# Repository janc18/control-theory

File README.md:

# Features
- Isolated plant
- Plant-ID, Plant cal-data (eeprom)
- USB-PD powered

# Design

# BOM
## Main Board

|Component|Price|Characteristics|
|--|--|--|
|[ST STM32H7R3V8T6](https://www.st.com/resource/en/datasheet/stm32h7r3a8.pdf)| 7.89 USD| 600 Mhz, 67 GPIO|
|[FTDI FT232HL](https://ftdichip.com/products/ft232hl/)|4.09 USD| USB Hi-Speed to Single Channel Serial UART/FIFO/JTAG/SPI/I2C IC, LQFP-48|
|[TX24-30R-6ST-H1E](https://www.jae.com/direct/topics/topics_file_download/?topics_id=66728&ext_no=06)|1.36 USD|Board-to-Board Connector, parallel/ vertical, 30 pos., 1.27mm pitch, Receptacle|
|[TX25-30P-6ST-H1E](https://www.jae.com/direct/topics/topics_file_download/?topics_id=66780&ext_no=06)|0.98 USD|Board-to-Board Connector, parallel/ vertical, 30 pos., 1.27mm pitch, Plug|
|USB type C Connector|||
|DC DC Converter|||
|Mix Components(Leds)|||
|[ST STUSB4500](https://www.st.com/resource/en/datasheet/stusb4500.pdf)|1.91 USD|Standalone USB PD sink controller with short-to-VBUS protections|
|[TI ISO7760](https://www.ti.com/lit/gpn/iso7760)|2.59 USD| Robust EMC, six-channel, 6/0, reinforced digital isolator|

## Connector power rails:
- 3.3 V: LDO generated
- 5 V: USB or Buck converter
- 12 V: PD (optional)
- 20 V: PD (optional)

## FT232HL
### Requirements
To use any kind of interface (SPI, I2c, JTAG, or a proprietary protocol) it's require to send commands down the data stream
- 12Mhz oscillator
- [External EEPROM - 93LC56BT-I/OT](https://ww1.microchip.com/downloads/en/DeviceDoc/21794G.pdf) 
- LC Filter

# INFO
[A Primer on USB Type-C® and USB Power Delivery Applications and Requirements](https://www.ti.com/lit/SLYY109B) \
[USB PD: Power Delivery for Your Next Project](https://resources.altium.com/p/usb-power-delivery-your-next-project) \
[AN232B-04 Data Throughput, Latency and Handshaking](https://ftdichip.com/wp-content/uploads/2020/08/AN232B-04_DataLatencyFlow.pdf)\
[FT2232D/H Fast Opto-Isolated Serial Interface Mode](https://www.ftdichip.com/Support/Documents/AppNotes/AN_131_FT2232D_H_Fast%20Opto-Isolated%20Serial%20Interface%20mode.pdf)\
[N2232-02 Bit Mode Functions for the FT223](https://www.ftdichip.com/Documents/AppNotes/AN2232C-02_FT2232CBitMode.pdf)\
[Examples  for the JTAG interface with Labview](https://ftdichip.com/software-examples/mpsse-projects/ftcjtag-examples/)

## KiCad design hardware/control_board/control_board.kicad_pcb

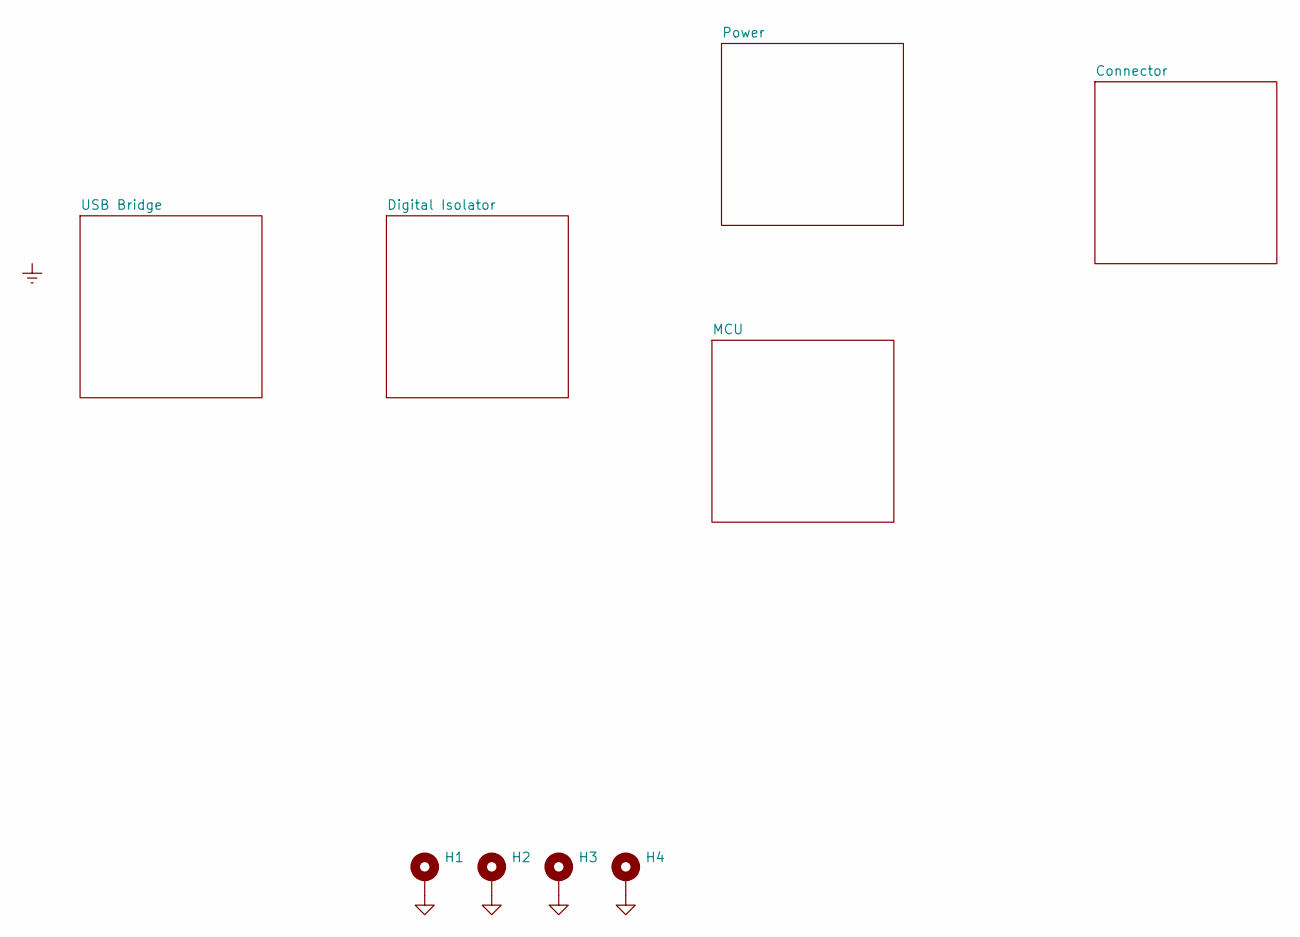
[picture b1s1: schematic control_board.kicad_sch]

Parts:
H1, H2, H3, H4: MountingHole_Pad; MountingHole_3.2mm_M3_Pad_Via

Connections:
GND: H1.1, H2.1, H3.1, H4.1

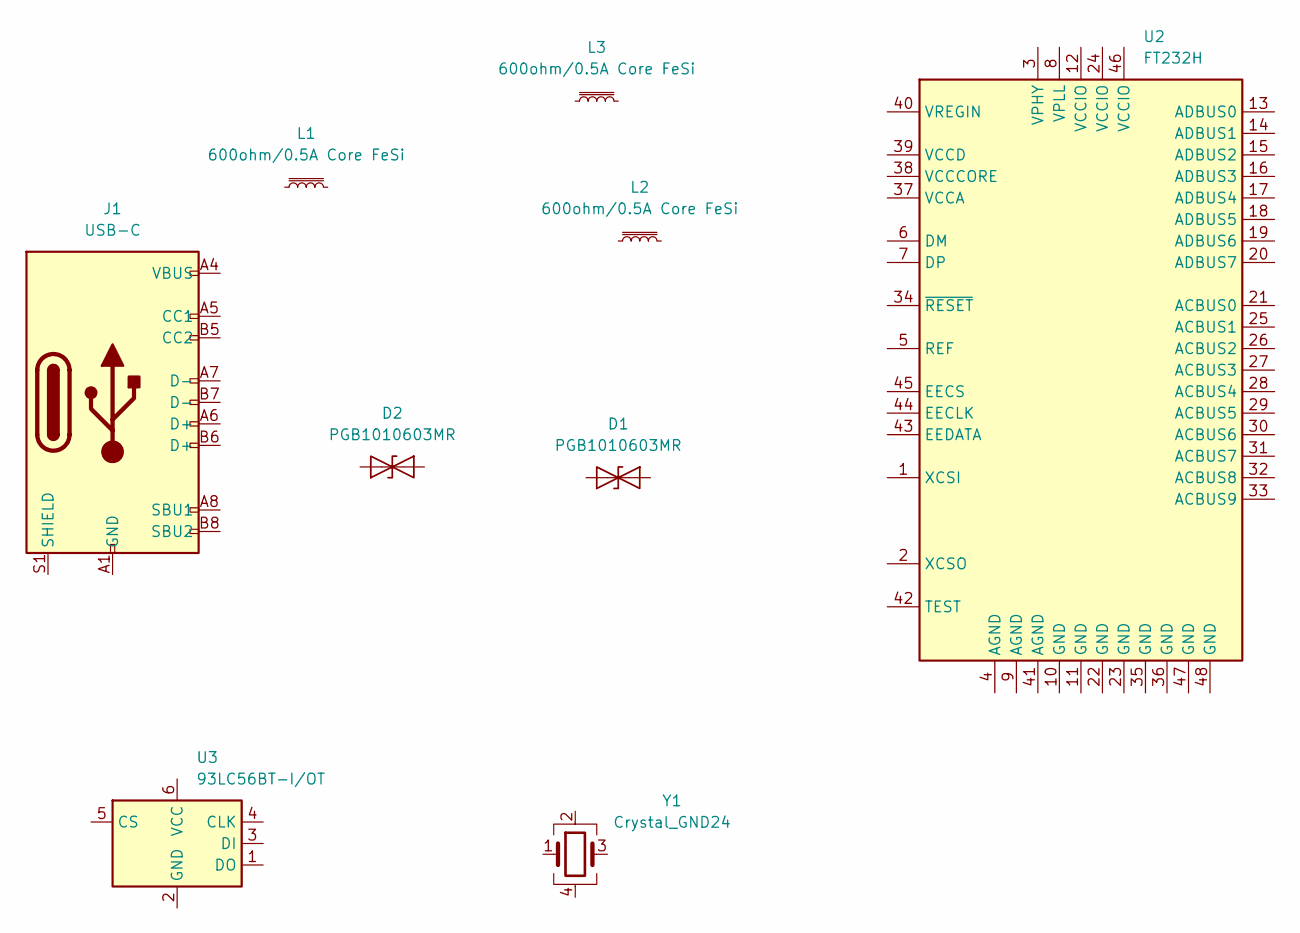
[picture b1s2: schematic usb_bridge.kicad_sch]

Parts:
D1, D2: PGB1010603MR; D_0603_1608Metric
J1: USB-C
L1, L2, L3: 600ohm/0.5A Core FeSi; L_0603_1608Metric
U2: FT232H; NXP_LQFN-48-1EP_7x7mm_P0.5mm_EP3.5x3.5mm_16xMask0.45x0.45
U3: 93LC56BT-I/OT; SOT-23-6
Y1: Crystal_GND24; Crystal_SMD_SeikoEpson_FA238V-4Pin_3.2x2.5mm

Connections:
unnamed: J1.A1 (GND), J1.A12 (GND), J1.B1 (GND), J1.B12 (GND)
unnamed: J1.A4 (VBUS), J1.A9 (VBUS), J1.B4 (VBUS), J1.B9 (VBUS)

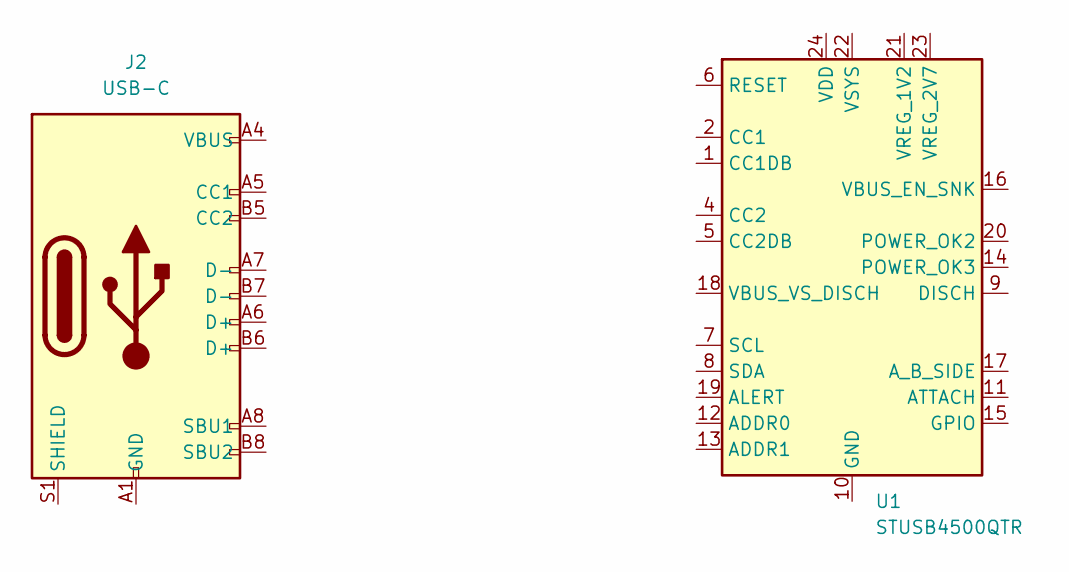
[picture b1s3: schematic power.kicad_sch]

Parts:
J2: USB-C
U1: STUSB4500QTR; QFN-24-1EP_4x4mm_P0.5mm_EP2.7x2.7mm

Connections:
unnamed: J2.A1 (GND), J2.A12 (GND), J2.B1 (GND), J2.B12 (GND)
unnamed: J2.A4 (VBUS), J2.A9 (VBUS), J2.B4 (VBUS), J2.B9 (VBUS)
unnamed: U1.10 (GND), U1.25 (GND)

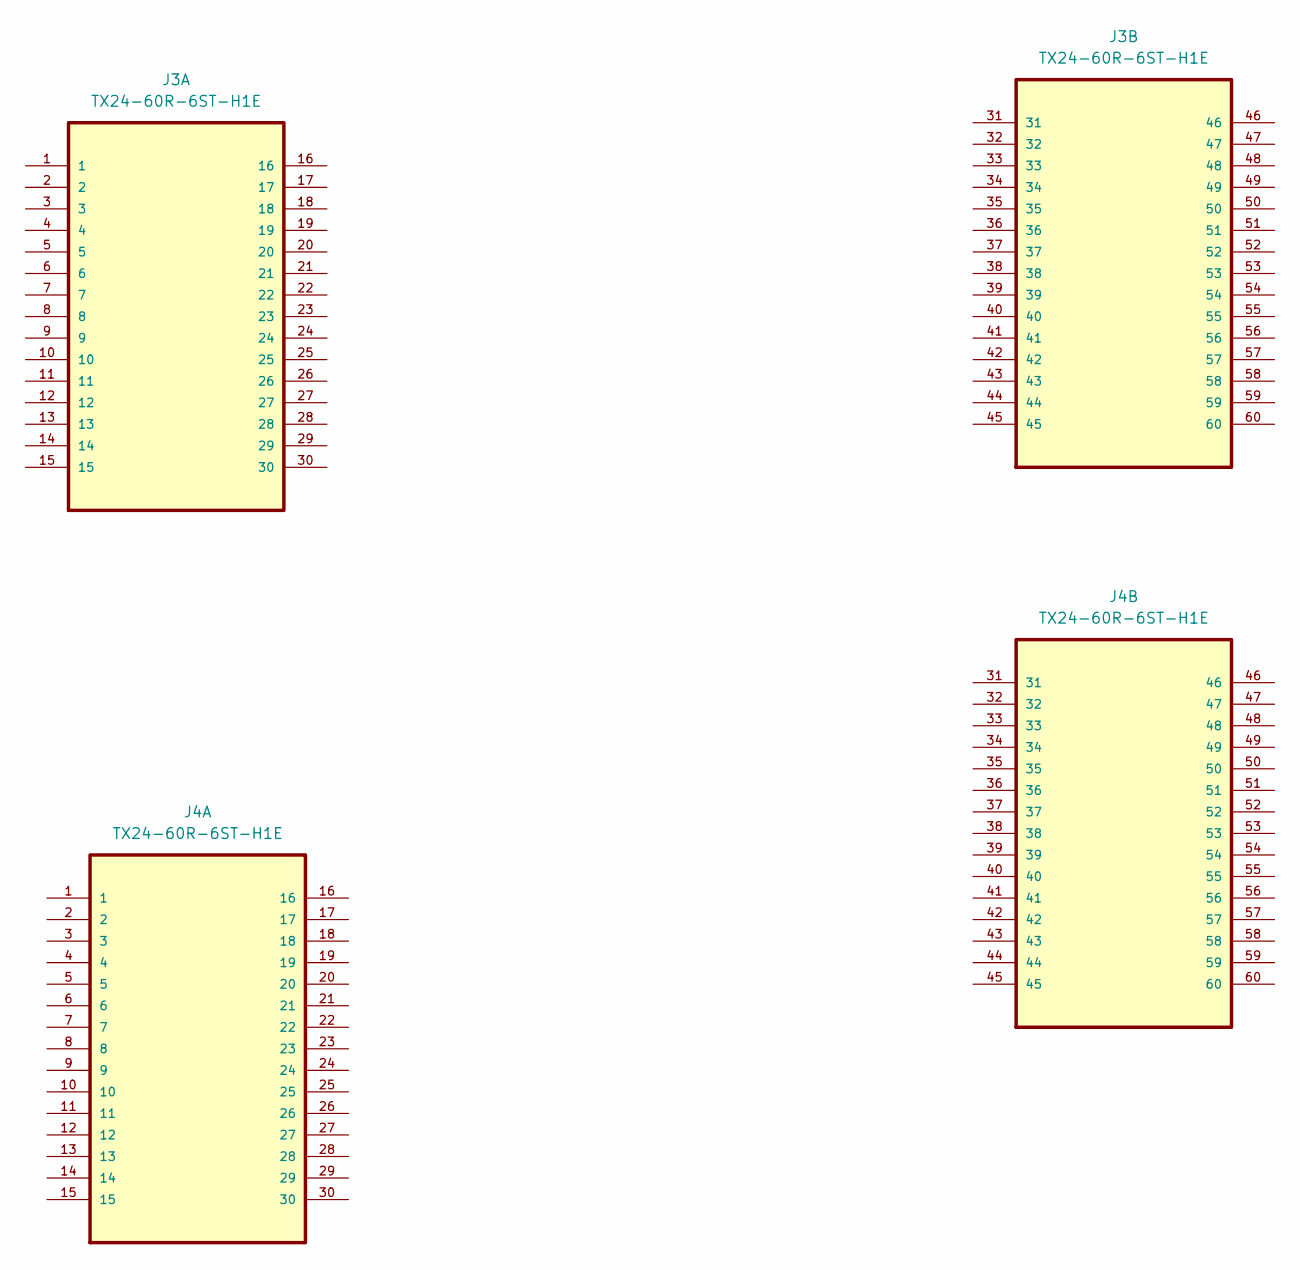
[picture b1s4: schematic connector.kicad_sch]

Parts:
J3, J4: TX24-60R-6ST-H1E; JAE_TX24-60R-6ST-H1E

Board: 4 copper layers, 17 parts (2 on the bottom side), 6 nets, no tracks yet.

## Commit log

2024-09-06 Update README.md
    added bom table
2024-09-08 added: FT232HL requirements
2024-09-08 added: a new line to each line
2024-09-08 added: EEPROM Part number
2024-09-21 hardware
2024-09-21 added: .gitignore
2024-09-21 dir restructuring
2024-09-21 added symbols and footprints
2024-09-22 added connectors
2024-09-22 deleted library.bak
2024-09-22 fixed 3d model paths, changed absolute paths to relative paths
2024-09-22 added components to uart bridge
